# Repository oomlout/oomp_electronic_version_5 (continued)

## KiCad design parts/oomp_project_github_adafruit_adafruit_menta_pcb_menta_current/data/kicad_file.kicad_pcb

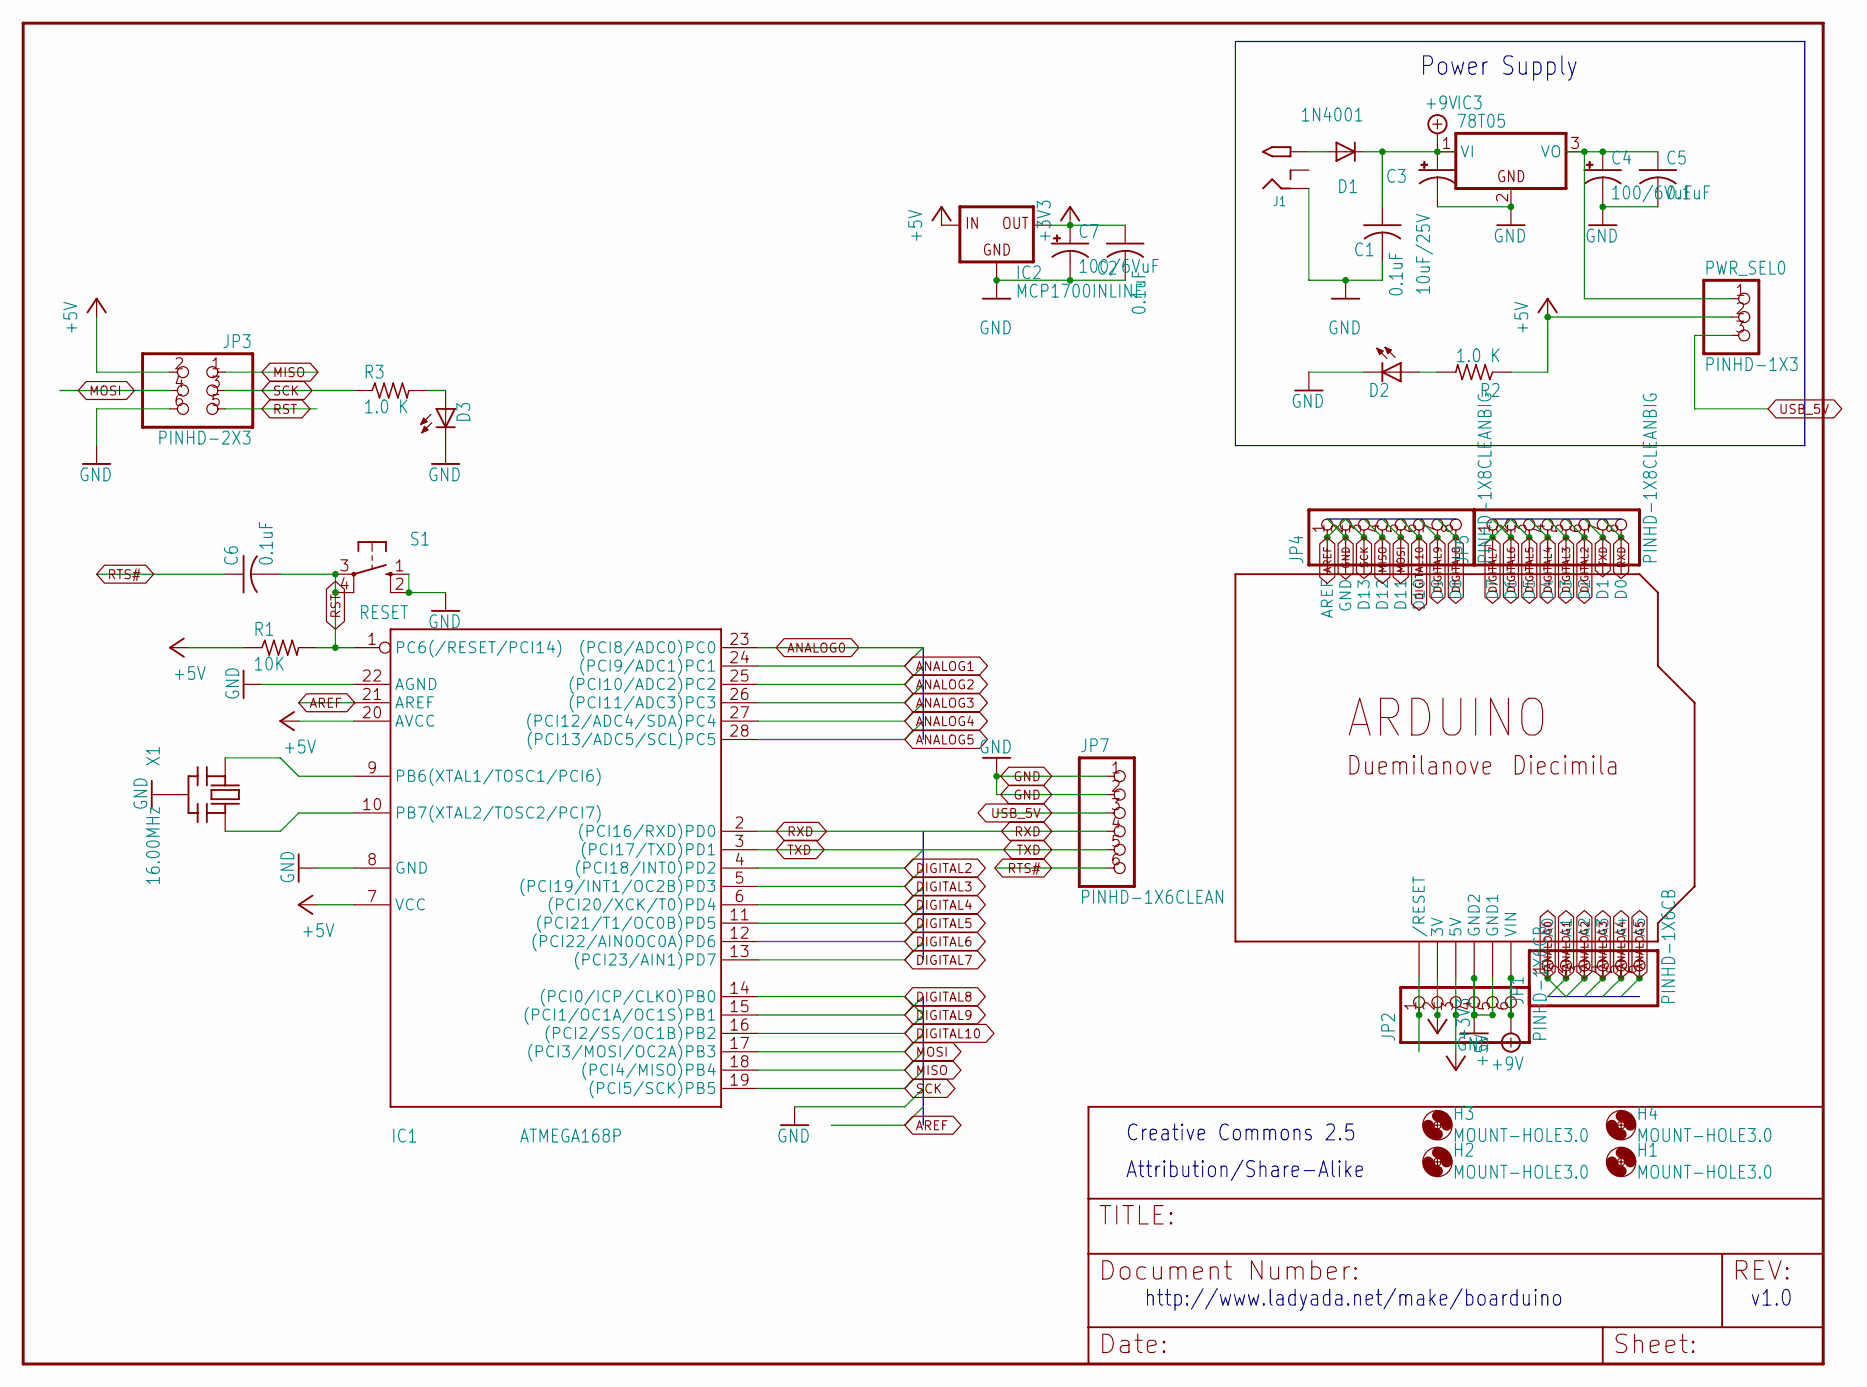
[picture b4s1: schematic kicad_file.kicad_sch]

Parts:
C1, C2, C5, C6: 0.1uF; C025-025X050
C3: 10uF/25V; E2,5-6
C4, C7: 100/6VuF; E2,5-6
D1: 1N4001; DO41-10
D2: LED3MM
D3: Green; LED3MM
H1, H2, H3, H4: MOUNT-HOLE3.0; 3,0
IC1: ATMEGA168P; DIL28_3
IC2: MCP1700INLINE; TO92-INLINE
IC3: 78T05; TO220H
J1: 2.1MMJACK; PJ-102A
JP1, JP2: PINHD-1X6CB; 1X06-CLEANBIG
JP3: PINHD-2X3; 2X03
JP4, JP5: PINHD-1X8CLEANBIG; 1X08-CLEANBIG
JP7: PINHD-1X6CLEAN; 1X06-CLEAN
PWR_SEL0: PINHD-1X3; 1X03
R1: 10K; 0207_10
R2, R3: 1.0 K; 0207_10
S1: RESET; B3F-10XX
U$2: ARDUINO-NOHOLE
X1: 16.00MHz; CERM_OSC

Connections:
+3V3: C2.1, C7.+, IC2.3 (OUT), JP2.2, U$2.3V
+5V: IC1.7 (VCC), IC1.20 (AVCC), IC2.2 (IN), JP2.3, JP3.2, PWR_SEL0.2, R1.1, R2.1, U$2.5V
+9V: C1.1, C3.+, D1.C, IC3.1 (VI), JP2.6, U$2.VIN
ANALOG0: IC1.23 ((PCI8/ADC0)PC0), JP1.1, U$2.A0
ANALOG1: IC1.24 ((PCI9/ADC1)PC1), JP1.2, U$2.A1
ANALOG2: IC1.25 ((PCI10/ADC2)PC2), JP1.3, U$2.A2
ANALOG3: IC1.26 ((PCI11/ADC3)PC3), JP1.4, U$2.A3
ANALOG4: IC1.27 ((PCI12/ADC4/SDA)PC4), JP1.5, U$2.A4
ANALOG5: IC1.28 ((PCI13/ADC5/SCL)PC5), JP1.6, U$2.A5
AREF: IC1.21 (AREF), JP4.1, U$2.AREF
DIGITAL2: IC1.4 ((PCI18/INT0)PD2), JP5.6, U$2.D2
DIGITAL3: IC1.5 ((PCI19/INT1/OC2B)PD3), JP5.5, U$2.D3
DIGITAL4: IC1.6 ((PCI20/XCK/T0)PD4), JP5.4, U$2.D4
DIGITAL5: IC1.11 ((PCI21/T1/OC0B)PD5), JP5.3, U$2.D5
DIGITAL6: IC1.12 ((PCI22/AIN0OC0A)PD6), JP5.2, U$2.D6
DIGITAL7: IC1.13 ((PCI23/AIN1)PD7), JP5.1, U$2.D7
DIGITAL8: IC1.14 ((PCI0/ICP/CLKO)PB0), JP4.8, U$2.D8
DIGITAL9: IC1.15 ((PCI1/OC1A/OC1S)PB1), JP4.7, U$2.D9
DIGITAL10: IC1.16 ((PCI2/SS/OC1B)PB2), JP4.6, U$2.D10
GND: C1.2, C2.2, C3.-, C4.-, C5.2, C7.-, D2.K (C), D3.K (C), IC1.8 (GND), IC1.22 (AGND), IC2.1 (GND), IC3.2 (GND), J1.RING, JP2.4, JP2.5, JP3.6, JP4.2, JP7.1, JP7.2, S1.1 (S), S1.2 (S1), U$2.GND, U$2.GND1, U$2.GND2, X1.P$2 (GND)
MISO: IC1.18 ((PCI4/MISO)PB4), JP3.1, JP4.4, U$2.D12
MOSI: IC1.17 ((PCI3/MOSI/OC2A)PB3), JP3.4, JP4.5, U$2.D11
unnamed: IC1.9 (PB6(XTAL1/TOSC1/PCI6)), X1.P$1 (IN)
unnamed: IC1.10 (PB7(XTAL2/TOSC2/PCI7)), X1.P$3 (OUT)
unnamed: D2.A, R2.2
unnamed: D3.A, R3.2
unnamed: C4.+, C5.1, IC3.3 (VO), PWR_SEL0.1
unnamed: D1.A, J1.TIP
RTS#: C6.1, JP7.6
RXD: IC1.2 ((PCI16/RXD)PD0), JP5.8, JP7.4, U$2.D0
SCK: IC1.19 ((PCI5/SCK)PB5), JP3.3, JP4.3, R3.1, U$2.D13
TXD: IC1.3 ((PCI17/TXD)PD1), JP5.7, JP7.5, U$2.D1
USB_5V: JP7.3, PWR_SEL0.3

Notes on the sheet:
Power Supply
v1.0
http://www.ladyada.net/make/boarduino
Attribution/Share-Alike
Creative Commons 2.5

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
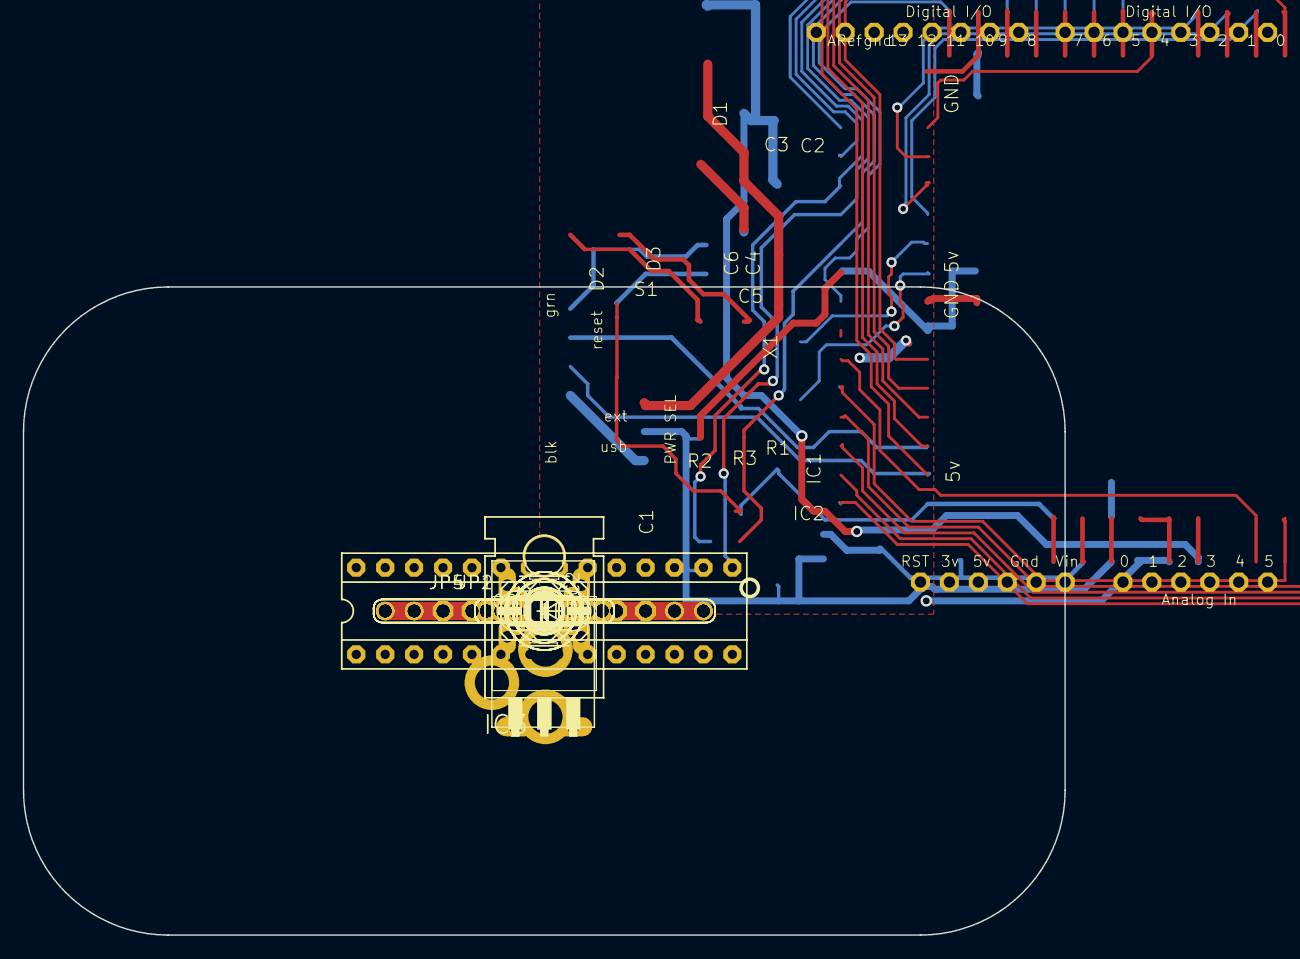
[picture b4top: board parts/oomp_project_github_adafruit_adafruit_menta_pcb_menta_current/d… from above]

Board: 16 copper layers, 91.4 x 56.9 mm, 60 parts (1 on the bottom side), 34 nets.

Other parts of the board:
U$3, U$4, U$5, U$6: 12-STRIP
U$7, U$8, U$9, U$10, U$11, U$12, U$13, U$14, U$15, U$16, U$17, U$18, U$19, U$20, U$21, U$22, U$23, U$24, U$25, U$26, U$27, U$28, U$29, U$30: 5-STRIP
U$31: ALTOIDSTIN-DIM

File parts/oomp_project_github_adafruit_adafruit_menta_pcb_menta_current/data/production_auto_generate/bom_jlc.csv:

Comment,Designator,Footprint,LCSC Part #
,PWR_SEL0,menta-import-fps:1X03,C49257
,JP7,menta-import-fps:1X06-CLEAN,C37208
,"JP1,JP2",menta-import-fps:1X06-CLEANBIG,C37208
,"JP4,JP5",menta-import-fps:1X08-CLEANBIG,C492421
,JP3,menta-import-fps:2X03,
,U$31,menta-import-fps:ALTOIDSTIN-DIM,
,D2,menta-import-fps:LED3MM,
,IC2,menta-import-fps:TO92-INLINE,
0.1uF,"C1,C2,C5,C6",menta-import-fps:C025-025X050,
1.0 K,"R2,R3",menta-import-fps:0207_10,
100/6VuF,"C4,C7","menta-import-fps:E2,5-6",
10K,R1,menta-import-fps:0207_10,
10uF/25V,C3,"menta-import-fps:E2,5-6",
1N4001,D1,menta-import-fps:DO41-10,
2.1MMJACK,J1,menta-import-fps:PJ-102A,
7805T,IC3,menta-import-fps:TO220H,
ARDUINO-NOHOLE,U$2,menta-import-fps:ARDUINO-NOHOLE,
ATMEGA168P,IC1,menta-import-fps:DIL28_3,
Green,D3,menta-import-fps:LED3MM,
RESET,S1,menta-import-fps:B3F-10XX,
